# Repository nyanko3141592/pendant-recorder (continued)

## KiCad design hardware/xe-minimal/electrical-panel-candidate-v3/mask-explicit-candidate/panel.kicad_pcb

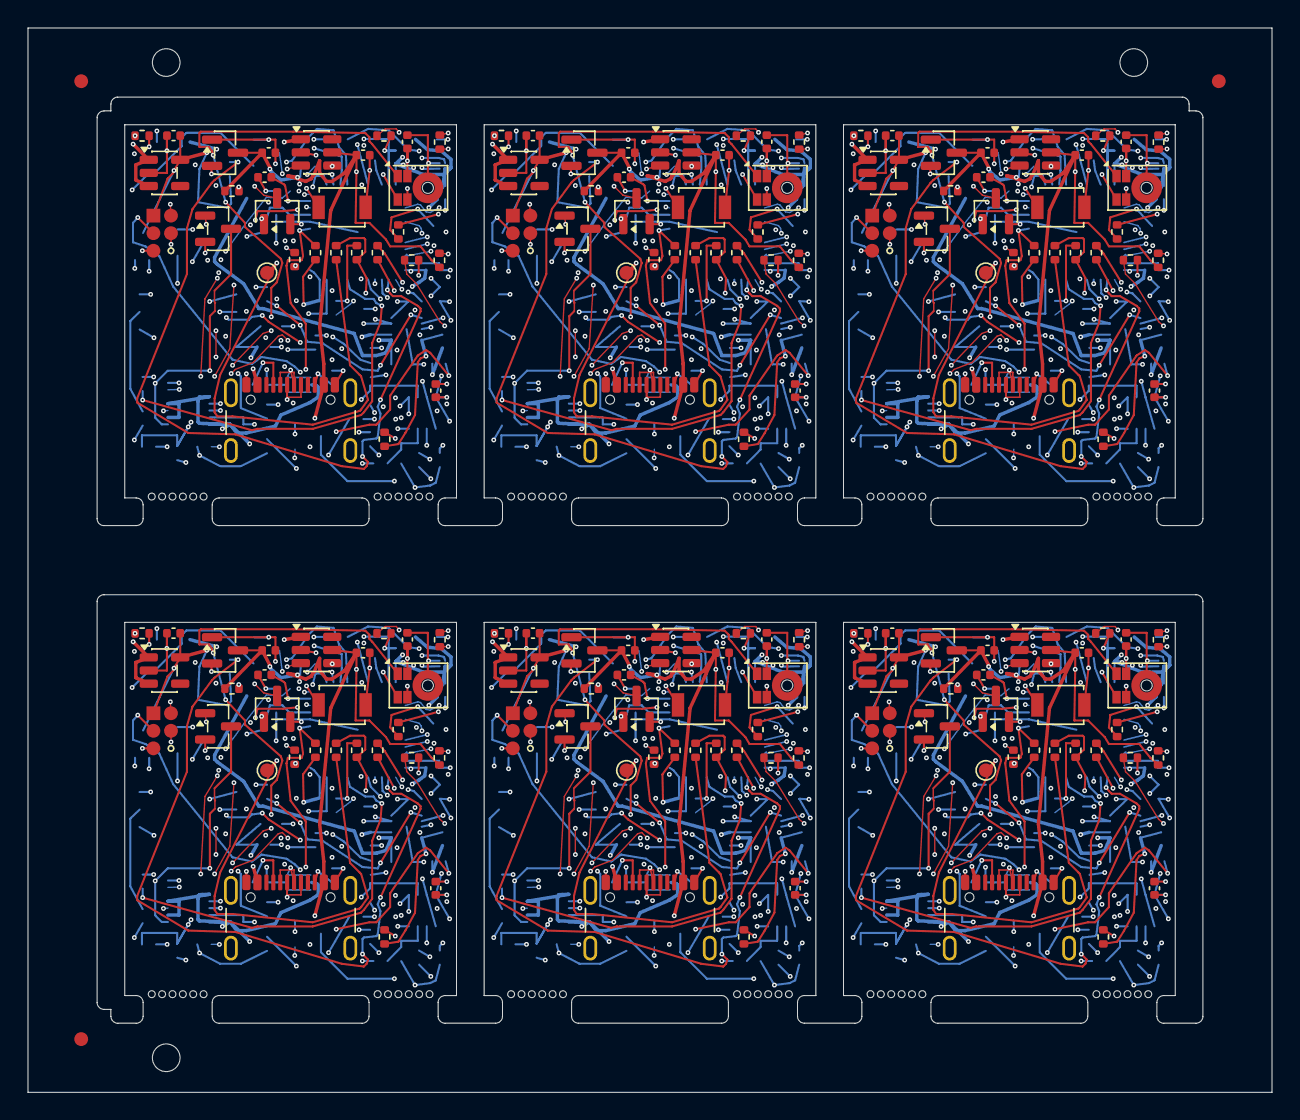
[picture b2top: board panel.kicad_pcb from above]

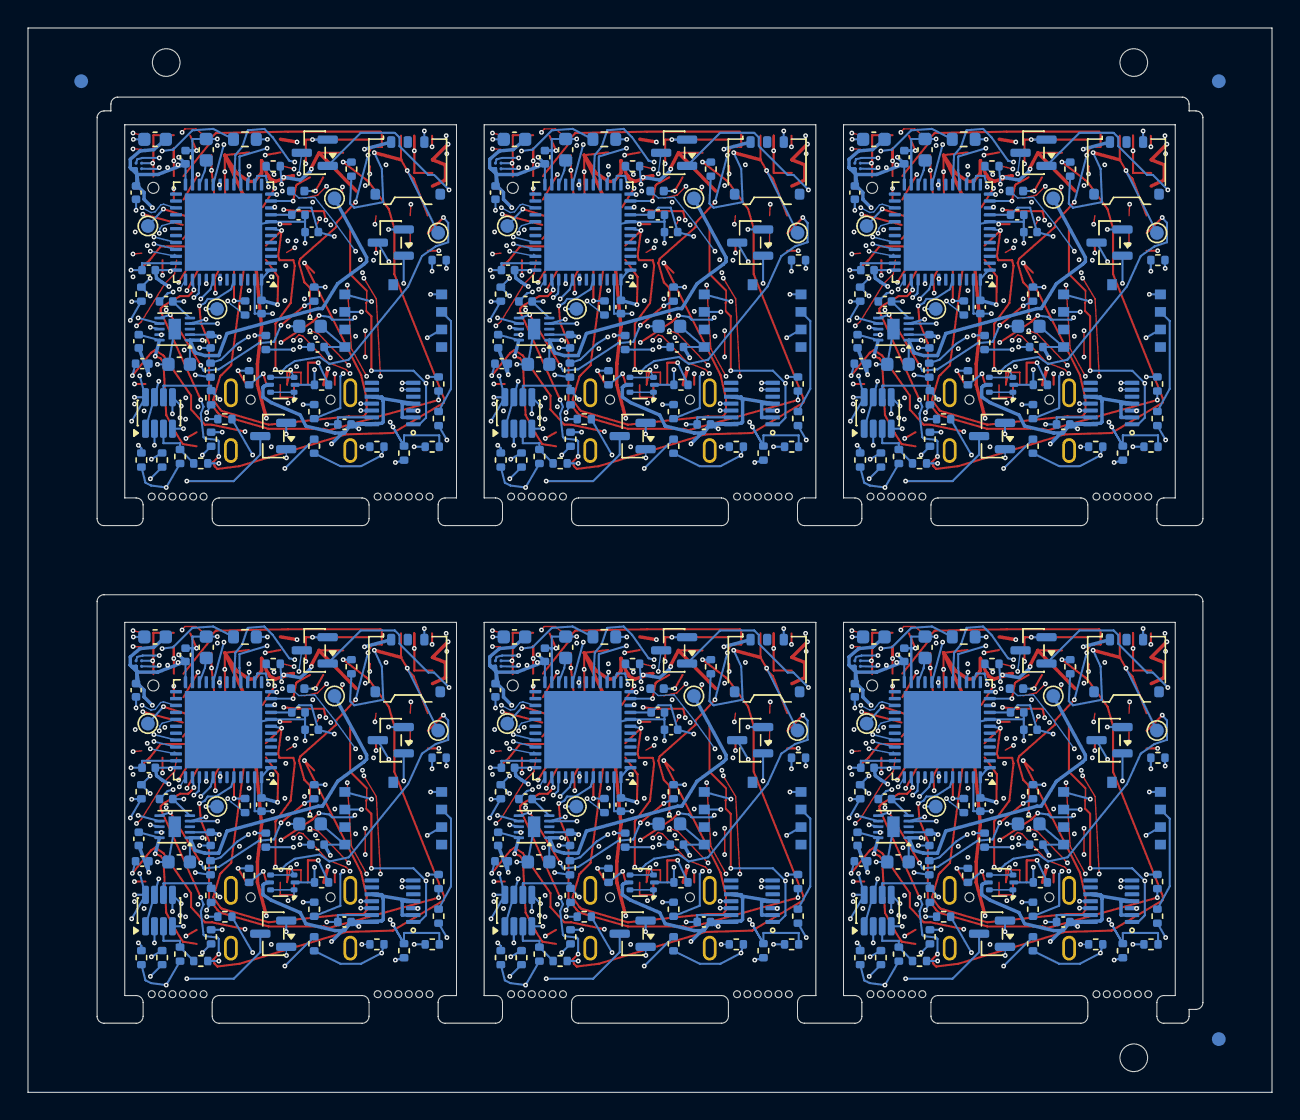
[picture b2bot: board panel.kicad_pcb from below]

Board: 6 copper layers, 90.0 x 77.0 mm, 531 parts (345 on the bottom side), 300 nets.

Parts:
FID1B, FID1F, FID2B, FID2F, FID3B, FID3F: (no value)
P1_C1, P1_C2, P1_C3, P1_C6, P1_C9, P1_C22, P1_C26, P2_C1, P2_C2, P2_C3, P2_C6, P2_C9, P2_C22, P2_C26, P3_C1, P3_C2, P3_C3, P3_C6, P3_C9, P3_C22, P3_C26, P4_C1, P4_C2, P4_C3, P4_C6, P4_C9, P4_C22, P4_C26, P5_C1, P5_C2, P5_C3, P5_C6, P5_C9, P5_C22, P5_C26, P6_C1, P6_C2, P6_C3, P6_C6, P6_C9, P6_C22, P6_C26: 100n; C_0402_1005Metric
P1_C4, P2_C4, P3_C4, P4_C4, P5_C4, P6_C4: 10u; C_0603_1608Metric
P1_C5, P2_C5, P3_C5, P4_C5, P5_C5, P6_C5: 4.7u; C_0603_1608Metric
P1_C7, P1_C16, P1_C25, P2_C7, P2_C16, P2_C25, P3_C7, P3_C16, P3_C25, P4_C7, P4_C16, P4_C25, P5_C7, P5_C16, P5_C25, P6_C7, P6_C16, P6_C25: 1u; C_0402_1005Metric
P1_C13, P2_C13, P3_C13, P4_C13, P5_C13, P6_C13: 2.2u 10V; C_0402_1005Metric
P1_C14, P2_C14, P3_C14, P4_C14, P5_C14, P6_C14: 2.2u; C_0402_1005Metric
P1_C15, P2_C15, P3_C15, P4_C15, P5_C15, P6_C15: 10u 10V effective >=1u; C_0603_1608Metric
P1_C27, P2_C27, P3_C27, P4_C27, P5_C27, P6_C27: 4.7u effective TBD; C_0603_1608Metric
P1_C28, P2_C28, P3_C28, P4_C28, P5_C28, P6_C28: 10n; C_0402_1005Metric
P1_C29, P1_C32, P1_C33, P2_C29, P2_C32, P2_C33, P3_C29, P3_C32, P3_C33, P4_C29, P4_C32, P4_C33, P5_C29, P5_C32, P5_C33, P6_C29, P6_C32, P6_C33: 100n 10V; C_0402_1005Metric
P1_C30, P2_C30, P3_C30, P4_C30, P5_C30, P6_C30: 50p 50V C0G; C_0402_1005Metric
P1_C31, P2_C31, P3_C31, P4_C31, P5_C31, P6_C31: 1u 10V; C_0402_1005Metric
P1_D6, P2_D6, P3_D6, P4_D6, P5_D6, P6_D6: amber LED 0402 TBD; LED_0402_1005Metric
P1_J1, P2_J1, P3_J1, P4_J1, P5_J1, P6_J1: USB4105-GF-A (candidate); USB_C_GCT_USB4105_GroundLand112
P1_J2, P2_J2, P3_J2, P4_J2, P5_J2, P6_J2: Molex781710003 / DTP401525-XE; Molex_Pico-EZmate_78171-0003_1x03-1MP_P1.20mm_Vertical
P1_J3, P2_J3, P3_J3, P4_J3, P5_J3, P6_J3: Factory SWD pogo candidate; SWD_Pogo_5Pad_P1.27mm
P1_Q3, P2_Q3, P3_Q3, P4_Q3, P5_Q3, P6_Q3: 2N7002 (VBUS detect); SOT-23
P1_Q4, P1_Q5, P1_Q6, P1_Q7, P2_Q4, P2_Q5, P2_Q6, P2_Q7, P3_Q4, P3_Q5, P3_Q6, P3_Q7, P4_Q4, P4_Q5, P4_Q6, P4_Q7, P5_Q4, P5_Q5, P5_Q6, P5_Q7, P6_Q4, P6_Q5, P6_Q6, P6_Q7: 2N7002; SOT-23
P1_R1, P2_R1, P3_R1, P4_R1, P5_R1, P6_R1: 0R; R_0402_1005Metric
P1_R2, P2_R2, P3_R2, P4_R2, P5_R2, P6_R2: 10k; R_0402_1005Metric
P1_R3, P1_R4, P1_R12, P1_R13, P1_R15, P1_R22, P1_R36, P2_R3, P2_R4, P2_R12, P2_R13, P2_R15, P2_R22, P2_R36, P3_R3, P3_R4, P3_R12, P3_R13, P3_R15, P3_R22, P3_R36, P4_R3, P4_R4, P4_R12, P4_R13, P4_R15, P4_R22, P4_R36, P5_R3, P5_R4, P5_R12, P5_R13, P5_R15, P5_R22, P5_R36, P6_R3, P6_R4, P6_R12, P6_R13, P6_R15, P6_R22, P6_R36: 100k; R_0402_1005Metric
P1_R6, P1_R7, P2_R6, P2_R7, P3_R6, P3_R7, P4_R6, P4_R7, P5_R6, P5_R7, P6_R6, P6_R7: 5.1k 1%; R_0402_1005Metric
P1_R10, P2_R10, P3_R10, P4_R10, P5_R10, P6_R10: 6.8k 1%; R_0402_1005Metric
P1_R11, P1_R39, P2_R11, P2_R39, P3_R11, P3_R39, P4_R11, P4_R39, P5_R11, P5_R39, P6_R11, P6_R39: 20k 1%; R_0402_1005Metric
P1_R14, P2_R14, P3_R14, P4_R14, P5_R14, P6_R14: 1M; R_0402_1005Metric
P1_R21, P1_R23, P2_R21, P2_R23, P3_R21, P3_R23, P4_R21, P4_R23, P5_R21, P5_R23, P6_R21, P6_R23: 22R tentative; R_0402_1005Metric
P1_R24, P1_R25, P1_R28, P2_R24, P2_R25, P2_R28, P3_R24, P3_R25, P3_R28, P4_R24, P4_R25, P4_R28, P5_R24, P5_R25, P5_R28, P6_R24, P6_R25, P6_R28: 47k; R_0402_1005Metric
P1_R32, P2_R32, P3_R32, P4_R32, P5_R32, P6_R32: 6.8k tentative; R_0402_1005Metric
P1_R33, P1_R34, P2_R33, P2_R34, P3_R33, P3_R34, P4_R33, P4_R34, P5_R33, P5_R34, P6_R33, P6_R34: 1M 1%; R_0402_1005Metric
P1_R35, P1_R43, P1_R47, P1_R48, P2_R35, P2_R43, P2_R47, P2_R48, P3_R35, P3_R43, P3_R47, P3_R48, P4_R35, P4_R43, P4_R47, P4_R48, P5_R35, P5_R43, P5_R47, P5_R48, P6_R35, P6_R43, P6_R47, P6_R48: 10k 1%; R_0402_1005Metric
P1_R37, P1_R38, P1_R40, P1_R45, P1_R46, P1_R49, P1_R50, P2_R37, P2_R38, P2_R40, P2_R45, P2_R46, P2_R49, P2_R50, P3_R37, P3_R38, P3_R40, P3_R45, P3_R46, P3_R49, P3_R50, P4_R37, P4_R38, P4_R40, P4_R45, P4_R46, P4_R49, P4_R50, P5_R37, P5_R38, P5_R40, P5_R45, P5_R46, P5_R49, P5_R50, P6_R37, P6_R38, P6_R40, P6_R45, P6_R46, P6_R49, P6_R50: 100k 1%; R_0402_1005Metric
P1_R41, P2_R41, P3_R41, P4_R41, P5_R41, P6_R41: 7.5k 1%; R_0402_1005Metric
P1_R42, P2_R42, P3_R42, P4_R42, P5_R42, P6_R42: 130k 1%; R_0402_1005Metric
P1_R44, P2_R44, P3_R44, P4_R44, P5_R44, P6_R44: 390k 1%; R_0402_1005Metric
P1_SW1, P2_SW1, P3_SW1, P4_SW1, P5_SW1, P6_SW1: B3U-1000P (candidate); SW_SPST_B3U-1000P
P1_TH1, P2_TH1, P3_TH1, P4_TH1, P5_TH1, P6_TH1: NCP18XH103F03RB 10k 1% B3380 candidate; R_0603_1608Metric
P1_TP1, P1_TP2, P1_TP3, P1_TP5, P1_TP6, P2_TP1, P2_TP2, P2_TP3, P2_TP5, P2_TP6, P3_TP1, P3_TP2, P3_TP3, P3_TP5, P3_TP6, P4_TP1, P4_TP2, P4_TP3, P4_TP5, P4_TP6, P5_TP1, P5_TP2, P5_TP3, P5_TP5, P5_TP6, P6_TP1, P6_TP2, P6_TP3, P6_TP5, P6_TP6: TestPoint; TestPoint_Pad_D1.0mm
P1_U1, P2_U1, P3_U1, P4_U1, P5_U1, P6_U1: STM32U535CEU6; QFN-48-1EP_7x7mm_P0.5mm_EP5.6x5.6mm
P1_U2, P2_U2, P3_U2, P4_U2, P5_U2, P6_U2: USBLC6-2P6; SOT-666
P1_U3, P2_U3, P3_U3, P4_U3, P5_U3, P6_U3: BQ25185DLHR; Texas_DLH0010A_WSON-10-1EP_2.2x2mm_P0.4mm_EP0.9x1.5mm
P1_U4, P2_U4, P3_U4, P4_U4, P5_U4, P6_U4: TPS7A0233PDBVR; SOT-23-5
P1_U8, P2_U8, P3_U8, P4_U8, P5_U8, P6_U8: IM69D130V01XTSA1; IM69D130_JLC_SMD_trial
P1_U10, P2_U10, P3_U10, P4_U10, P5_U10, P6_U10: TPS22916CYFPR; TPS22916_YFP4
P1_U11, P2_U11, P3_U11, P4_U11, P5_U11, P6_U11: CSNP32GCR01-BOW candidate; CSNP32GCR01_LGA8
P1_U12, P2_U12, P3_U12, P4_U12, P5_U12, P6_U12: TLV7042DDFR; SOT-23-8
P1_U13, P2_U13, P3_U13, P4_U13, P5_U13, P6_U13: MAX4995CAUT+T; SOT-23-6
P1_U14, P2_U14, P3_U14, P4_U14, P5_U14, P6_U14: SN74HCS74DYYR; Texas_DYY0014A
P1_U15, P2_U15, P3_U15, P4_U15, P5_U15, P6_U15: TLV803EB29DBZR; SOT-23
PERF1, PERF2, PERF3, PERF4, PERF5, PERF6: (no value)
TOOL1, TOOL2, TOOL3: (no value)

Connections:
P1/BAT: P1_C14.1, P1_J2.1, P1_R33.1, P1_TP1.1, P1_U3.2
P1/BAT_ADC: P1_C28.1, P1_R33.2, P1_R34.1, P1_U1.11
P1/BAT_TS: P1_R37.2, P1_TH1.1, P1_U12.2, P1_U12.5
P1/BOOT0: P1_R3.1, P1_U1.44
P1/BUTTON_N: P1_R4.2, P1_SW1.1, P1_U1.38
P1/CC1: P1_J1.A5, P1_R6.1
P1/CC2: P1_J1.B5, P1_R7.1
P1/CHARGER_TS: P1_R35.1, P1_U3.6
P1/CHG_ALLOW: P1_R43.1, P1_U1.20
P1/CHG_GUARD_GATE: P1_Q4.1, P1_R36.1, P1_R43.2, P1_U12.1, P1_U12.7
P1/CHG_INHIBIT_GATE: P1_Q4.3, P1_R12.2, P1_U3.4
P1/CHG_N: P1_R11.2, P1_U1.27, P1_U3.9
P1/GND: P1_C1.2, P1_C2.2, P1_C3.2, P1_C4.2, P1_C5.2, P1_C6.2, P1_C7.2, P1_C9.2, P1_C13.2, P1_C14.2, P1_C15.2, P1_C16.2, P1_C22.2, P1_C25.2, P1_C26.2, P1_C27.2, P1_C28.2, P1_C29.2, P1_C30.2, P1_C31.2, P1_C32.2, P1_C33.2, P1_D6.1, P1_J1.A1, P1_J1.A12, P1_J1.B1, P1_J1.B12, P1_J1.SH, P1_J2.3, P1_J3.5, P1_Q3.2, P1_Q4.2, P1_Q5.2, P1_Q6.2, P1_Q7.2, P1_R3.2, P1_R6.2, P1_R7.2, P1_R10.2, P1_R14.2, P1_R22.2, P1_R34.2, P1_R35.2, P1_R36.2, P1_R39.2, P1_R41.2, P1_R42.2, P1_R44.2, P1_R46.2, P1_R49.2, P1_R50.2, P1_SW1.2, P1_TH1.2, P1_TP6.1, P1_U1.8, P1_U1.23, P1_U1.35, P1_U1.47, P1_U1.49, P1_U2.2, P1_U3.5, P1_U3.11, P1_U4.2, P1_U8.4, P1_U8.5, P1_U10.B1, P1_U11.4, P1_U12.4, P1_U13.2, P1_U14.7, P1_U14.11, P1_U14.12, P1_U14.13, P1_U15.1
P1/ILIM_VSET: P1_R42.1, P1_U3.7
P1/ISET: P1_C30.1, P1_R10.1, P1_U3.8
P1/NRST: P1_C9.1, P1_J3.3, P1_R2.2, P1_U1.7
P1/PDM_CLK: P1_R21.2, P1_U8.3
P1/PDM_CLK_MCU: P1_R21.1, P1_U1.39
P1/PDM_DATA: P1_U1.40, P1_U8.1
P1/SD_CLK: P1_R23.2, P1_U11.3
P1/SD_CLK_MCU: P1_R23.1, P1_U1.15
P1/SD_CS_N: P1_R28.2, P1_U1.14, P1_U11.2
P1/SD_EN: P1_R22.1, P1_U1.41, P1_U10.B2
P1/SD_MISO: P1_R25.2, P1_U1.16, P1_U11.6
P1/SD_MOSI: P1_R24.2, P1_U1.17, P1_U11.5
P1/SD_V3: P1_C26.1, P1_C27.1, P1_R24.1, P1_R25.1, P1_R28.1, P1_TP5.1, P1_U10.A1, P1_U11.8
P1/STATUS_LED: P1_R32.1, P1_U1.29
P1/STATUS_LED_A: P1_D6.2, P1_R32.2
P1/SWCLK: P1_J3.4, P1_U1.37
P1/SWDIO: P1_J3.2, P1_U1.34
P1/SYS: P1_C15.1, P1_TP2.1, P1_U3.1, P1_U4.1, P1_U4.3
P1/TS_COLD_REF: P1_R38.2, P1_R39.1, P1_U12.3
P1/TS_HOT_REF: P1_R40.2, P1_R41.1, P1_U12.6
P1/USB_DM: P1_J1.A7, P1_J1.B7, P1_U1.32, P1_U2.3, P1_U2.4
P1/USB_DP: P1_J1.A6, P1_J1.B6, P1_U1.33, P1_U2.1, P1_U2.6
P1/USB_HIGH_BUDGET: P1_Q5.1, P1_R46.1, P1_U1.42
P1/USB_HIGH_BUDGET_DRAIN: P1_Q5.3, P1_R45.2
P1/USB_ILIM_SET: P1_R44.1, P1_R45.1, P1_U13.3
P1/USB_INPUT_ON: P1_U13.4, P1_U14.6
P1/USB_LATCH_CLEAR_N: P1_Q7.3, P1_R48.2, P1_U14.1, P1_U15.2
P1/USB_LATCH_CLOCK: P1_Q6.3, P1_R47.2, P1_U14.3
P1/USB_RESUME_PULSE: P1_Q7.1, P1_R50.1, P1_U1.19
P1/USB_SUSPEND_PULSE: P1_Q6.1, P1_R49.1, P1_U1.12
P1/V3V3: P1_C1.1, P1_C2.1, P1_C3.1, P1_C4.1, P1_C16.1, P1_C22.1, P1_C25.1, P1_C29.1, P1_J3.1, P1_R1.1, P1_R2.1, P1_R4.1, P1_R11.1, P1_R15.1, P1_R37.1, P1_R38.1, P1_R40.1, P1_TP3.1, P1_U1.1, P1_U1.24, P1_U1.36, P1_U1.48, P1_U4.5, P1_U8.2, P1_U10.A2, P1_U12.8
P1/VBUS: P1_C31.1, P1_C32.1, P1_C33.1, P1_J1.A4, P1_J1.A9, P1_J1.B4, P1_J1.B9, P1_R13.1, P1_R47.1, P1_R48.1, P1_U2.5, P1_U13.5, P1_U14.2, P1_U14.4, P1_U14.10, P1_U14.14, P1_U15.3
P1/VBUS_GATE: P1_Q3.1, P1_R13.2, P1_R14.1
P1/VBUS_LIMITED: P1_C13.1, P1_R12.1, P1_U3.10, P1_U13.1
P1/VBUS_N: P1_Q3.3, P1_R15.2, P1_U1.10
P1/VCAP: P1_C5.1, P1_U1.22
P1/VDDA: P1_C6.1, P1_C7.1, P1_R1.2, P1_U1.9
P2/BAT: P2_C14.1, P2_J2.1, P2_R33.1, P2_TP1.1, P2_U3.2
P2/BAT_ADC: P2_C28.1, P2_R33.2, P2_R34.1, P2_U1.11
P2/BAT_TS: P2_R37.2, P2_TH1.1, P2_U12.2, P2_U12.5
P2/BOOT0: P2_R3.1, P2_U1.44
P2/BUTTON_N: P2_R4.2, P2_SW1.1, P2_U1.38
P2/CC1: P2_J1.A5, P2_R6.1
P2/CC2: P2_J1.B5, P2_R7.1
P2/CHARGER_TS: P2_R35.1, P2_U3.6
P2/CHG_ALLOW: P2_R43.1, P2_U1.20
P2/CHG_GUARD_GATE: P2_Q4.1, P2_R36.1, P2_R43.2, P2_U12.1, P2_U12.7
P2/CHG_INHIBIT_GATE: P2_Q4.3, P2_R12.2, P2_U3.4
P2/CHG_N: P2_R11.2, P2_U1.27, P2_U3.9
P2/GND: P2_C1.2, P2_C2.2, P2_C3.2, P2_C4.2, P2_C5.2, P2_C6.2, P2_C7.2, P2_C9.2, P2_C13.2, P2_C14.2, P2_C15.2, P2_C16.2, P2_C22.2, P2_C25.2, P2_C26.2, P2_C27.2, P2_C28.2, P2_C29.2, P2_C30.2, P2_C31.2, P2_C32.2, P2_C33.2, P2_D6.1, P2_J1.A1, P2_J1.A12, P2_J1.B1, P2_J1.B12, P2_J1.SH, P2_J2.3, P2_J3.5, P2_Q3.2, P2_Q4.2, P2_Q5.2, P2_Q6.2, P2_Q7.2, P2_R3.2, P2_R6.2, P2_R7.2, P2_R10.2, P2_R14.2, P2_R22.2, P2_R34.2, P2_R35.2, P2_R36.2, P2_R39.2, P2_R41.2, P2_R42.2, P2_R44.2, P2_R46.2, P2_R49.2, P2_R50.2, P2_SW1.2, P2_TH1.2, P2_TP6.1, P2_U1.8, P2_U1.23, P2_U1.35, P2_U1.47, P2_U1.49, P2_U2.2, P2_U3.5, P2_U3.11, P2_U4.2, P2_U8.4, P2_U8.5, P2_U10.B1, P2_U11.4, P2_U12.4, P2_U13.2, P2_U14.7, P2_U14.11, P2_U14.12, P2_U14.13, P2_U15.1
P2/ILIM_VSET: P2_R42.1, P2_U3.7
P2/ISET: P2_C30.1, P2_R10.1, P2_U3.8
P2/NRST: P2_C9.1, P2_J3.3, P2_R2.2, P2_U1.7
P2/PDM_CLK: P2_R21.2, P2_U8.3
P2/PDM_CLK_MCU: P2_R21.1, P2_U1.39
P2/PDM_DATA: P2_U1.40, P2_U8.1
P2/SD_CLK: P2_R23.2, P2_U11.3
P2/SD_CLK_MCU: P2_R23.1, P2_U1.15
P2/SD_CS_N: P2_R28.2, P2_U1.14, P2_U11.2
P2/SD_EN: P2_R22.1, P2_U1.41, P2_U10.B2
P2/SD_MISO: P2_R25.2, P2_U1.16, P2_U11.6
P2/SD_MOSI: P2_R24.2, P2_U1.17, P2_U11.5
P2/SD_V3: P2_C26.1, P2_C27.1, P2_R24.1, P2_R25.1, P2_R28.1, P2_TP5.1, P2_U10.A1, P2_U11.8
P2/STATUS_LED: P2_R32.1, P2_U1.29
P2/STATUS_LED_A: P2_D6.2, P2_R32.2
P2/SWCLK: P2_J3.4, P2_U1.37
P2/SWDIO: P2_J3.2, P2_U1.34
P2/SYS: P2_C15.1, P2_TP2.1, P2_U3.1, P2_U4.1, P2_U4.3
P2/TS_COLD_REF: P2_R38.2, P2_R39.1, P2_U12.3
P2/TS_HOT_REF: P2_R40.2, P2_R41.1, P2_U12.6
P2/USB_DM: P2_J1.A7, P2_J1.B7, P2_U1.32, P2_U2.3, P2_U2.4
P2/USB_DP: P2_J1.A6, P2_J1.B6, P2_U1.33, P2_U2.1, P2_U2.6
P2/USB_HIGH_BUDGET: P2_Q5.1, P2_R46.1, P2_U1.42
P2/USB_HIGH_BUDGET_DRAIN: P2_Q5.3, P2_R45.2
P2/USB_ILIM_SET: P2_R44.1, P2_R45.1, P2_U13.3
P2/USB_INPUT_ON: P2_U13.4, P2_U14.6
P2/USB_LATCH_CLEAR_N: P2_Q7.3, P2_R48.2, P2_U14.1, P2_U15.2
P2/USB_LATCH_CLOCK: P2_Q6.3, P2_R47.2, P2_U14.3
P2/USB_RESUME_PULSE: P2_Q7.1, P2_R50.1, P2_U1.19
P2/USB_SUSPEND_PULSE: P2_Q6.1, P2_R49.1, P2_U1.12
P2/V3V3: P2_C1.1, P2_C2.1, P2_C3.1, P2_C4.1, P2_C16.1, P2_C22.1, P2_C25.1, P2_C29.1, P2_J3.1, P2_R1.1, P2_R2.1, P2_R4.1, P2_R11.1, P2_R15.1, P2_R37.1, P2_R38.1, P2_R40.1, P2_TP3.1, P2_U1.1, P2_U1.24, P2_U1.36, P2_U1.48, P2_U4.5, P2_U8.2, P2_U10.A2, P2_U12.8
P2/VBUS: P2_C31.1, P2_C32.1, P2_C33.1, P2_J1.A4, P2_J1.A9, P2_J1.B4, P2_J1.B9, P2_R13.1, P2_R47.1, P2_R48.1, P2_U2.5, P2_U13.5, P2_U14.2, P2_U14.4, P2_U14.10, P2_U14.14, P2_U15.3
P2/VBUS_GATE: P2_Q3.1, P2_R13.2, P2_R14.1
P2/VBUS_LIMITED: P2_C13.1, P2_R12.1, P2_U3.10, P2_U13.1
P2/VBUS_N: P2_Q3.3, P2_R15.2, P2_U1.10
P2/VCAP: P2_C5.1, P2_U1.22
P2/VDDA: P2_C6.1, P2_C7.1, P2_R1.2, P2_U1.9
P3/BAT: P3_C14.1, P3_J2.1, P3_R33.1, P3_TP1.1, P3_U3.2
P3/BAT_ADC: P3_C28.1, P3_R33.2, P3_R34.1, P3_U1.11
P3/BAT_TS: P3_R37.2, P3_TH1.1, P3_U12.2, P3_U12.5
P3/BOOT0: P3_R3.1, P3_U1.44
P3/BUTTON_N: P3_R4.2, P3_SW1.1, P3_U1.38
P3/CC1: P3_J1.A5, P3_R6.1
P3/CC2: P3_J1.B5, P3_R7.1
P3/CHARGER_TS: P3_R35.1, P3_U3.6
P3/CHG_ALLOW: P3_R43.1, P3_U1.20
P3/CHG_GUARD_GATE: P3_Q4.1, P3_R36.1, P3_R43.2, P3_U12.1, P3_U12.7
P3/CHG_INHIBIT_GATE: P3_Q4.3, P3_R12.2, P3_U3.4
P3/CHG_N: P3_R11.2, P3_U1.27, P3_U3.9
P3/GND: P3_C1.2, P3_C2.2, P3_C3.2, P3_C4.2, P3_C5.2, P3_C6.2, P3_C7.2, P3_C9.2, P3_C13.2, P3_C14.2, P3_C15.2, P3_C16.2, P3_C22.2, P3_C25.2, P3_C26.2, P3_C27.2, P3_C28.2, P3_C29.2, P3_C30.2, P3_C31.2, P3_C32.2, P3_C33.2, P3_D6.1, P3_J1.A1, P3_J1.A12, P3_J1.B1, P3_J1.B12, P3_J1.SH, P3_J2.3, P3_J3.5, P3_Q3.2, P3_Q4.2, P3_Q5.2, P3_Q6.2, P3_Q7.2, P3_R3.2, P3_R6.2, P3_R7.2, P3_R10.2, P3_R14.2, P3_R22.2, P3_R34.2, P3_R35.2, P3_R36.2, P3_R39.2, P3_R41.2, P3_R42.2, P3_R44.2, P3_R46.2, P3_R49.2, P3_R50.2, P3_SW1.2, P3_TH1.2, P3_TP6.1, P3_U1.8, P3_U1.23, P3_U1.35, P3_U1.47, P3_U1.49, P3_U2.2, P3_U3.5, P3_U3.11, P3_U4.2, P3_U8.4, P3_U8.5, P3_U10.B1, P3_U11.4, P3_U12.4, P3_U13.2, P3_U14.7, P3_U14.11, P3_U14.12, P3_U14.13, P3_U15.1
P3/ILIM_VSET: P3_R42.1, P3_U3.7
P3/ISET: P3_C30.1, P3_R10.1, P3_U3.8
P3/NRST: P3_C9.1, P3_J3.3, P3_R2.2, P3_U1.7
P3/PDM_CLK: P3_R21.2, P3_U8.3
P3/PDM_CLK_MCU: P3_R21.1, P3_U1.39
P3/PDM_DATA: P3_U1.40, P3_U8.1
P3/SD_CLK: P3_R23.2, P3_U11.3
P3/SD_CLK_MCU: P3_R23.1, P3_U1.15
P3/SD_CS_N: P3_R28.2, P3_U1.14, P3_U11.2
P3/SD_EN: P3_R22.1, P3_U1.41, P3_U10.B2
P3/SD_MISO: P3_R25.2, P3_U1.16, P3_U11.6
P3/SD_MOSI: P3_R24.2, P3_U1.17, P3_U11.5
P3/SD_V3: P3_C26.1, P3_C27.1, P3_R24.1, P3_R25.1, P3_R28.1, P3_TP5.1, P3_U10.A1, P3_U11.8
P3/STATUS_LED: P3_R32.1, P3_U1.29
P3/STATUS_LED_A: P3_D6.2, P3_R32.2
P3/SWCLK: P3_J3.4, P3_U1.37
P3/SWDIO: P3_J3.2, P3_U1.34
P3/SYS: P3_C15.1, P3_TP2.1, P3_U3.1, P3_U4.1, P3_U4.3
P3/TS_COLD_REF: P3_R38.2, P3_R39.1, P3_U12.3
P3/TS_HOT_REF: P3_R40.2, P3_R41.1, P3_U12.6
P3/USB_DM: P3_J1.A7, P3_J1.B7, P3_U1.32, P3_U2.3, P3_U2.4
P3/USB_DP: P3_J1.A6, P3_J1.B6, P3_U1.33, P3_U2.1, P3_U2.6
P3/USB_HIGH_BUDGET: P3_Q5.1, P3_R46.1, P3_U1.42
P3/USB_HIGH_BUDGET_DRAIN: P3_Q5.3, P3_R45.2
P3/USB_ILIM_SET: P3_R44.1, P3_R45.1, P3_U13.3
P3/USB_INPUT_ON: P3_U13.4, P3_U14.6
P3/USB_LATCH_CLEAR_N: P3_Q7.3, P3_R48.2, P3_U14.1, P3_U15.2
P3/USB_LATCH_CLOCK: P3_Q6.3, P3_R47.2, P3_U14.3
P3/USB_RESUME_PULSE: P3_Q7.1, P3_R50.1, P3_U1.19
P3/USB_SUSPEND_PULSE: P3_Q6.1, P3_R49.1, P3_U1.12
P3/V3V3: P3_C1.1, P3_C2.1, P3_C3.1, P3_C4.1, P3_C16.1, P3_C22.1, P3_C25.1, P3_C29.1, P3_J3.1, P3_R1.1, P3_R2.1, P3_R4.1, P3_R11.1, P3_R15.1, P3_R37.1, P3_R38.1, P3_R40.1, P3_TP3.1, P3_U1.1, P3_U1.24, P3_U1.36, P3_U1.48, P3_U4.5, P3_U8.2, P3_U10.A2, P3_U12.8
P3/VBUS: P3_C31.1, P3_C32.1, P3_C33.1, P3_J1.A4, P3_J1.A9, P3_J1.B4, P3_J1.B9, P3_R13.1, P3_R47.1, P3_R48.1, P3_U2.5, P3_U13.5, P3_U14.2, P3_U14.4, P3_U14.10, P3_U14.14, P3_U15.3
P3/VBUS_GATE: P3_Q3.1, P3_R13.2, P3_R14.1
P3/VBUS_LIMITED: P3_C13.1, P3_R12.1, P3_U3.10, P3_U13.1
P3/VBUS_N: P3_Q3.3, P3_R15.2, P3_U1.10
P3/VCAP: P3_C5.1, P3_U1.22
P3/VDDA: P3_C6.1, P3_C7.1, P3_R1.2, P3_U1.9
P4/BAT: P4_C14.1, P4_J2.1, P4_R33.1, P4_TP1.1, P4_U3.2
P4/BAT_ADC: P4_C28.1, P4_R33.2, P4_R34.1, P4_U1.11
P4/BAT_TS: P4_R37.2, P4_TH1.1, P4_U12.2, P4_U12.5
P4/BOOT0: P4_R3.1, P4_U1.44
P4/BUTTON_N: P4_R4.2, P4_SW1.1, P4_U1.38
P4/CC1: P4_J1.A5, P4_R6.1
P4/CC2: P4_J1.B5, P4_R7.1
P4/CHARGER_TS: P4_R35.1, P4_U3.6
P4/CHG_ALLOW: P4_R43.1, P4_U1.20
P4/CHG_GUARD_GATE: P4_Q4.1, P4_R36.1, P4_R43.2, P4_U12.1, P4_U12.7
P4/CHG_INHIBIT_GATE: P4_Q4.3, P4_R12.2, P4_U3.4
P4/CHG_N: P4_R11.2, P4_U1.27, P4_U3.9
P4/GND: P4_C1.2, P4_C2.2, P4_C3.2, P4_C4.2, P4_C5.2, P4_C6.2, P4_C7.2, P4_C9.2, P4_C13.2, P4_C14.2, P4_C15.2, P4_C16.2, P4_C22.2, P4_C25.2, P4_C26.2, P4_C27.2, P4_C28.2, P4_C29.2, P4_C30.2, P4_C31.2, P4_C32.2, P4_C33.2, P4_D6.1, P4_J1.A1, P4_J1.A12, P4_J1.B1, P4_J1.B12, P4_J1.SH, P4_J2.3, P4_J3.5, P4_Q3.2, P4_Q4.2, P4_Q5.2, P4_Q6.2, P4_Q7.2, P4_R3.2, P4_R6.2, P4_R7.2, P4_R10.2, P4_R14.2, P4_R22.2, P4_R34.2, P4_R35.2, P4_R36.2, P4_R39.2, P4_R41.2, P4_R42.2, P4_R44.2, P4_R46.2, P4_R49.2, P4_R50.2, P4_SW1.2, P4_TH1.2, P4_TP6.1, P4_U1.8, P4_U1.23, P4_U1.35, P4_U1.47, P4_U1.49, P4_U2.2, P4_U3.5, P4_U3.11, P4_U4.2, P4_U8.4, P4_U8.5, P4_U10.B1, P4_U11.4, P4_U12.4, P4_U13.2, P4_U14.7, P4_U14.11, P4_U14.12, P4_U14.13, P4_U15.1
P4/ILIM_VSET: P4_R42.1, P4_U3.7
P4/ISET: P4_C30.1, P4_R10.1, P4_U3.8
P4/NRST: P4_C9.1, P4_J3.3, P4_R2.2, P4_U1.7
P4/PDM_CLK: P4_R21.2, P4_U8.3
P4/PDM_CLK_MCU: P4_R21.1, P4_U1.39
P4/PDM_DATA: P4_U1.40, P4_U8.1
P4/SD_CLK: P4_R23.2, P4_U11.3
P4/SD_CLK_MCU: P4_R23.1, P4_U1.15
P4/SD_CS_N: P4_R28.2, P4_U1.14, P4_U11.2
P4/SD_EN: P4_R22.1, P4_U1.41, P4_U10.B2
P4/SD_MISO: P4_R25.2, P4_U1.16, P4_U11.6
P4/SD_MOSI: P4_R24.2, P4_U1.17, P4_U11.5
P4/SD_V3: P4_C26.1, P4_C27.1, P4_R24.1, P4_R25.1, P4_R28.1, P4_TP5.1, P4_U10.A1, P4_U11.8
P4/STATUS_LED: P4_R32.1, P4_U1.29
P4/STATUS_LED_A: P4_D6.2, P4_R32.2
P4/SWCLK: P4_J3.4, P4_U1.37
P4/SWDIO: P4_J3.2, P4_U1.34
P4/SYS: P4_C15.1, P4_TP2.1, P4_U3.1, P4_U4.1, P4_U4.3
P4/TS_COLD_REF: P4_R38.2, P4_R39.1, P4_U12.3
P4/TS_HOT_REF: P4_R40.2, P4_R41.1, P4_U12.6
P4/USB_DM: P4_J1.A7, P4_J1.B7, P4_U1.32, P4_U2.3, P4_U2.4
P4/USB_DP: P4_J1.A6, P4_J1.B6, P4_U1.33, P4_U2.1, P4_U2.6
P4/USB_HIGH_BUDGET: P4_Q5.1, P4_R46.1, P4_U1.42
P4/USB_HIGH_BUDGET_DRAIN: P4_Q5.3, P4_R45.2
P4/USB_ILIM_SET: P4_R44.1, P4_R45.1, P4_U13.3
P4/USB_INPUT_ON: P4_U13.4, P4_U14.6
P4/USB_LATCH_CLEAR_N: P4_Q7.3, P4_R48.2, P4_U14.1, P4_U15.2
P4/USB_LATCH_CLOCK: P4_Q6.3, P4_R47.2, P4_U14.3
P4/USB_RESUME_PULSE: P4_Q7.1, P4_R50.1, P4_U1.19
P4/USB_SUSPEND_PULSE: P4_Q6.1, P4_R49.1, P4_U1.12
P4/V3V3: P4_C1.1, P4_C2.1, P4_C3.1, P4_C4.1, P4_C16.1, P4_C22.1, P4_C25.1, P4_C29.1, P4_J3.1, P4_R1.1, P4_R2.1, P4_R4.1, P4_R11.1, P4_R15.1, P4_R37.1, P4_R38.1, P4_R40.1, P4_TP3.1, P4_U1.1, P4_U1.24, P4_U1.36, P4_U1.48, P4_U4.5, P4_U8.2, P4_U10.A2, P4_U12.8
P4/VBUS: P4_C31.1, P4_C32.1, P4_C33.1, P4_J1.A4, P4_J1.A9, P4_J1.B4, P4_J1.B9, P4_R13.1, P4_R47.1, P4_R48.1, P4_U2.5, P4_U13.5, P4_U14.2, P4_U14.4, P4_U14.10, P4_U14.14, P4_U15.3
P4/VBUS_GATE: P4_Q3.1, P4_R13.2, P4_R14.1
P4/VBUS_LIMITED: P4_C13.1, P4_R12.1, P4_U3.10, P4_U13.1
P4/VBUS_N: P4_Q3.3, P4_R15.2, P4_U1.10
P4/VCAP: P4_C5.1, P4_U1.22
P4/VDDA: P4_C6.1, P4_C7.1, P4_R1.2, P4_U1.9
P5/BAT: P5_C14.1, P5_J2.1, P5_R33.1, P5_TP1.1, P5_U3.2
P5/BAT_ADC: P5_C28.1, P5_R33.2, P5_R34.1, P5_U1.11
P5/BAT_TS: P5_R37.2, P5_TH1.1, P5_U12.2, P5_U12.5
P5/BOOT0: P5_R3.1, P5_U1.44
P5/BUTTON_N: P5_R4.2, P5_SW1.1, P5_U1.38
P5/CC1: P5_J1.A5, P5_R6.1
P5/CC2: P5_J1.B5, P5_R7.1
P5/CHARGER_TS: P5_R35.1, P5_U3.6
P5/CHG_ALLOW: P5_R43.1, P5_U1.20
P5/CHG_GUARD_GATE: P5_Q4.1, P5_R36.1, P5_R43.2, P5_U12.1, P5_U12.7
P5/CHG_INHIBIT_GATE: P5_Q4.3, P5_R12.2, P5_U3.4
P5/CHG_N: P5_R11.2, P5_U1.27, P5_U3.9
P5/GND: P5_C1.2, P5_C2.2, P5_C3.2, P5_C4.2, P5_C5.2, P5_C6.2, P5_C7.2, P5_C9.2, P5_C13.2, P5_C14.2, P5_C15.2, P5_C16.2, P5_C22.2, P5_C25.2, P5_C26.2, P5_C27.2, P5_C28.2, P5_C29.2, P5_C30.2, P5_C31.2, P5_C32.2, P5_C33.2, P5_D6.1, P5_J1.A1, P5_J1.A12, P5_J1.B1, P5_J1.B12, P5_J1.SH, P5_J2.3, P5_J3.5, P5_Q3.2, P5_Q4.2, P5_Q5.2, P5_Q6.2, P5_Q7.2, P5_R3.2, P5_R6.2, P5_R7.2, P5_R10.2, P5_R14.2, P5_R22.2, P5_R34.2, P5_R35.2, P5_R36.2, P5_R39.2, P5_R41.2, P5_R42.2, P5_R44.2, P5_R46.2, P5_R49.2, P5_R50.2, P5_SW1.2, P5_TH1.2, P5_TP6.1, P5_U1.8, P5_U1.23, P5_U1.35, P5_U1.47, P5_U1.49, P5_U2.2, P5_U3.5, P5_U3.11, P5_U4.2, P5_U8.4, P5_U8.5, P5_U10.B1, P5_U11.4, P5_U12.4, P5_U13.2, P5_U14.7, P5_U14.11, P5_U14.12, P5_U14.13, P5_U15.1
P5/ILIM_VSET: P5_R42.1, P5_U3.7
P5/ISET: P5_C30.1, P5_R10.1, P5_U3.8
P5/NRST: P5_C9.1, P5_J3.3, P5_R2.2, P5_U1.7
P5/PDM_CLK: P5_R21.2, P5_U8.3
P5/PDM_CLK_MCU: P5_R21.1, P5_U1.39
P5/PDM_DATA: P5_U1.40, P5_U8.1
P5/SD_CLK: P5_R23.2, P5_U11.3
P5/SD_CLK_MCU: P5_R23.1, P5_U1.15
P5/SD_CS_N: P5_R28.2, P5_U1.14, P5_U11.2
P5/SD_EN: P5_R22.1, P5_U1.41, P5_U10.B2
P5/SD_MISO: P5_R25.2, P5_U1.16, P5_U11.6
P5/SD_MOSI: P5_R24.2, P5_U1.17, P5_U11.5
P5/SD_V3: P5_C26.1, P5_C27.1, P5_R24.1, P5_R25.1, P5_R28.1, P5_TP5.1, P5_U10.A1, P5_U11.8
P5/STATUS_LED: P5_R32.1, P5_U1.29
P5/STATUS_LED_A: P5_D6.2, P5_R32.2
P5/SWCLK: P5_J3.4, P5_U1.37
P5/SWDIO: P5_J3.2, P5_U1.34
P5/SYS: P5_C15.1, P5_TP2.1, P5_U3.1, P5_U4.1, P5_U4.3
P5/TS_COLD_REF: P5_R38.2, P5_R39.1, P5_U12.3
P5/TS_HOT_REF: P5_R40.2, P5_R41.1, P5_U12.6
P5/USB_DM: P5_J1.A7, P5_J1.B7, P5_U1.32, P5_U2.3, P5_U2.4
P5/USB_DP: P5_J1.A6, P5_J1.B6, P5_U1.33, P5_U2.1, P5_U2.6
P5/USB_HIGH_BUDGET: P5_Q5.1, P5_R46.1, P5_U1.42
P5/USB_HIGH_BUDGET_DRAIN: P5_Q5.3, P5_R45.2
P5/USB_ILIM_SET: P5_R44.1, P5_R45.1, P5_U13.3
P5/USB_INPUT_ON: P5_U13.4, P5_U14.6
P5/USB_LATCH_CLEAR_N: P5_Q7.3, P5_R48.2, P5_U14.1, P5_U15.2
P5/USB_LATCH_CLOCK: P5_Q6.3, P5_R47.2, P5_U14.3
P5/USB_RESUME_PULSE: P5_Q7.1, P5_R50.1, P5_U1.19
P5/USB_SUSPEND_PULSE: P5_Q6.1, P5_R49.1, P5_U1.12
P5/V3V3: P5_C1.1, P5_C2.1, P5_C3.1, P5_C4.1, P5_C16.1, P5_C22.1, P5_C25.1, P5_C29.1, P5_J3.1, P5_R1.1, P5_R2.1, P5_R4.1, P5_R11.1, P5_R15.1, P5_R37.1, P5_R38.1, P5_R40.1, P5_TP3.1, P5_U1.1, P5_U1.24, P5_U1.36, P5_U1.48, P5_U4.5, P5_U8.2, P5_U10.A2, P5_U12.8
P5/VBUS: P5_C31.1, P5_C32.1, P5_C33.1, P5_J1.A4, P5_J1.A9, P5_J1.B4, P5_J1.B9, P5_R13.1, P5_R47.1, P5_R48.1, P5_U2.5, P5_U13.5, P5_U14.2, P5_U14.4, P5_U14.10, P5_U14.14, P5_U15.3
P5/VBUS_GATE: P5_Q3.1, P5_R13.2, P5_R14.1
P5/VBUS_LIMITED: P5_C13.1, P5_R12.1, P5_U3.10, P5_U13.1
P5/VBUS_N: P5_Q3.3, P5_R15.2, P5_U1.10
P5/VCAP: P5_C5.1, P5_U1.22
P5/VDDA: P5_C6.1, P5_C7.1, P5_R1.2, P5_U1.9
P6/BAT: P6_C14.1, P6_J2.1, P6_R33.1, P6_TP1.1, P6_U3.2
P6/BAT_ADC: P6_C28.1, P6_R33.2, P6_R34.1, P6_U1.11
P6/BAT_TS: P6_R37.2, P6_TH1.1, P6_U12.2, P6_U12.5
P6/BOOT0: P6_R3.1, P6_U1.44
P6/BUTTON_N: P6_R4.2, P6_SW1.1, P6_U1.38
P6/CC1: P6_J1.A5, P6_R6.1
P6/CC2: P6_J1.B5, P6_R7.1
P6/CHARGER_TS: P6_R35.1, P6_U3.6
P6/CHG_ALLOW: P6_R43.1, P6_U1.20
P6/CHG_GUARD_GATE: P6_Q4.1, P6_R36.1, P6_R43.2, P6_U12.1, P6_U12.7
P6/CHG_INHIBIT_GATE: P6_Q4.3, P6_R12.2, P6_U3.4
P6/CHG_N: P6_R11.2, P6_U1.27, P6_U3.9
P6/GND: P6_C1.2, P6_C2.2, P6_C3.2, P6_C4.2, P6_C5.2, P6_C6.2, P6_C7.2, P6_C9.2, P6_C13.2, P6_C14.2, P6_C15.2, P6_C16.2, P6_C22.2, P6_C25.2, P6_C26.2, P6_C27.2, P6_C28.2, P6_C29.2, P6_C30.2, P6_C31.2, P6_C32.2, P6_C33.2, P6_D6.1, P6_J1.A1, P6_J1.A12, P6_J1.B1, P6_J1.B12, P6_J1.SH, P6_J2.3, P6_J3.5, P6_Q3.2, P6_Q4.2, P6_Q5.2, P6_Q6.2, P6_Q7.2, P6_R3.2, P6_R6.2, P6_R7.2, P6_R10.2, P6_R14.2, P6_R22.2, P6_R34.2, P6_R35.2, P6_R36.2, P6_R39.2, P6_R41.2, P6_R42.2, P6_R44.2, P6_R46.2, P6_R49.2, P6_R50.2, P6_SW1.2, P6_TH1.2, P6_TP6.1, P6_U1.8, P6_U1.23, P6_U1.35, P6_U1.47, P6_U1.49, P6_U2.2, P6_U3.5, P6_U3.11, P6_U4.2, P6_U8.4, P6_U8.5, P6_U10.B1, P6_U11.4, P6_U12.4, P6_U13.2, P6_U14.7, P6_U14.11, P6_U14.12, P6_U14.13, P6_U15.1
P6/ILIM_VSET: P6_R42.1, P6_U3.7
P6/ISET: P6_C30.1, P6_R10.1, P6_U3.8
P6/NRST: P6_C9.1, P6_J3.3, P6_R2.2, P6_U1.7
P6/PDM_CLK: P6_R21.2, P6_U8.3
P6/PDM_CLK_MCU: P6_R21.1, P6_U1.39
P6/PDM_DATA: P6_U1.40, P6_U8.1
P6/SD_CLK: P6_R23.2, P6_U11.3
P6/SD_CLK_MCU: P6_R23.1, P6_U1.15
P6/SD_CS_N: P6_R28.2, P6_U1.14, P6_U11.2
P6/SD_EN: P6_R22.1, P6_U1.41, P6_U10.B2
P6/SD_MISO: P6_R25.2, P6_U1.16, P6_U11.6
P6/SD_MOSI: P6_R24.2, P6_U1.17, P6_U11.5
P6/SD_V3: P6_C26.1, P6_C27.1, P6_R24.1, P6_R25.1, P6_R28.1, P6_TP5.1, P6_U10.A1, P6_U11.8
P6/STATUS_LED: P6_R32.1, P6_U1.29
P6/STATUS_LED_A: P6_D6.2, P6_R32.2
P6/SWCLK: P6_J3.4, P6_U1.37
P6/SWDIO: P6_J3.2, P6_U1.34
P6/SYS: P6_C15.1, P6_TP2.1, P6_U3.1, P6_U4.1, P6_U4.3
P6/TS_COLD_REF: P6_R38.2, P6_R39.1, P6_U12.3
P6/TS_HOT_REF: P6_R40.2, P6_R41.1, P6_U12.6
P6/USB_DM: P6_J1.A7, P6_J1.B7, P6_U1.32, P6_U2.3, P6_U2.4
P6/USB_DP: P6_J1.A6, P6_J1.B6, P6_U1.33, P6_U2.1, P6_U2.6
P6/USB_HIGH_BUDGET: P6_Q5.1, P6_R46.1, P6_U1.42
P6/USB_HIGH_BUDGET_DRAIN: P6_Q5.3, P6_R45.2
P6/USB_ILIM_SET: P6_R44.1, P6_R45.1, P6_U13.3
P6/USB_INPUT_ON: P6_U13.4, P6_U14.6
P6/USB_LATCH_CLEAR_N: P6_Q7.3, P6_R48.2, P6_U14.1, P6_U15.2
P6/USB_LATCH_CLOCK: P6_Q6.3, P6_R47.2, P6_U14.3
P6/USB_RESUME_PULSE: P6_Q7.1, P6_R50.1, P6_U1.19
P6/USB_SUSPEND_PULSE: P6_Q6.1, P6_R49.1, P6_U1.12
P6/V3V3: P6_C1.1, P6_C2.1, P6_C3.1, P6_C4.1, P6_C16.1, P6_C22.1, P6_C25.1, P6_C29.1, P6_J3.1, P6_R1.1, P6_R2.1, P6_R4.1, P6_R11.1, P6_R15.1, P6_R37.1, P6_R38.1, P6_R40.1, P6_TP3.1, P6_U1.1, P6_U1.24, P6_U1.36, P6_U1.48, P6_U4.5, P6_U8.2, P6_U10.A2, P6_U12.8
P6/VBUS: P6_C31.1, P6_C32.1, P6_C33.1, P6_J1.A4, P6_J1.A9, P6_J1.B4, P6_J1.B9, P6_R13.1, P6_R47.1, P6_R48.1, P6_U2.5, P6_U13.5, P6_U14.2, P6_U14.4, P6_U14.10, P6_U14.14, P6_U15.3
P6/VBUS_GATE: P6_Q3.1, P6_R13.2, P6_R14.1
P6/VBUS_LIMITED: P6_C13.1, P6_R12.1, P6_U3.10, P6_U13.1
P6/VBUS_N: P6_Q3.3, P6_R15.2, P6_U1.10
P6/VCAP: P6_C5.1, P6_U1.22
P6/VDDA: P6_C6.1, P6_C7.1, P6_R1.2, P6_U1.9
